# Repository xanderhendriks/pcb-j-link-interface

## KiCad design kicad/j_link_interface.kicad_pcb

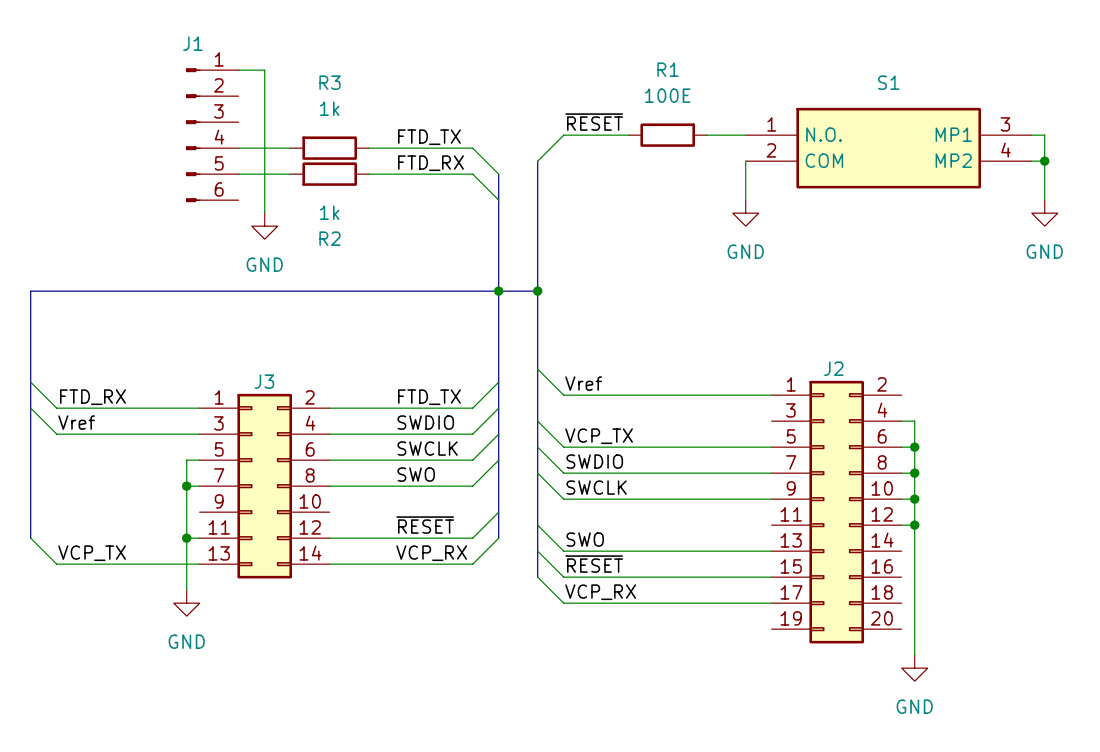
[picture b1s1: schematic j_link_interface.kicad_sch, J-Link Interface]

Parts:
J1: Conn_01x05_Pin; PinHeader_1x06_P2.54mm_Vertical; LCSC C3347142
J2: SFH11-PBPC-D10-RA-BK; LCSC C3319874
J3: FTSH-107-01-X-DV-K; SAMTEC_FTSH-107-01-X-DV-K; LCSC C5307809
R1: 100E; R_0603_1608Metric; LCSC C22775
R2, R3: 1k; R_0603_1608Metric; LCSC C21190
S1: EVQP4HB3B; Manufacturer_Part_Number EVQP42B3M; LCSC C485511

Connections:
/FTD_RX: J3.1, R2.1
/FTD_TX: J3.2, R3.1
/SWCLK: J2.9, J3.6
/SWDIO: J2.7, J3.4
/SWO: J2.13, J3.8
/VCP_RX: J2.17, J3.14
/VCP_TX: J2.5, J3.13
/Vref: J2.1, J3.3
/~RESET: J2.15, J3.12, R1.1
GND: J1.1, J2.4, J2.6, J2.8, J2.10, J2.12, J3.5, J3.7, J3.11, S1.2 (COM), S1.3 (MP1), S1.4 (MP2)
unnamed: J1.4, R3.2
unnamed: J1.5, R2.2
unnamed: R1.2, S1.1 (N.O.)

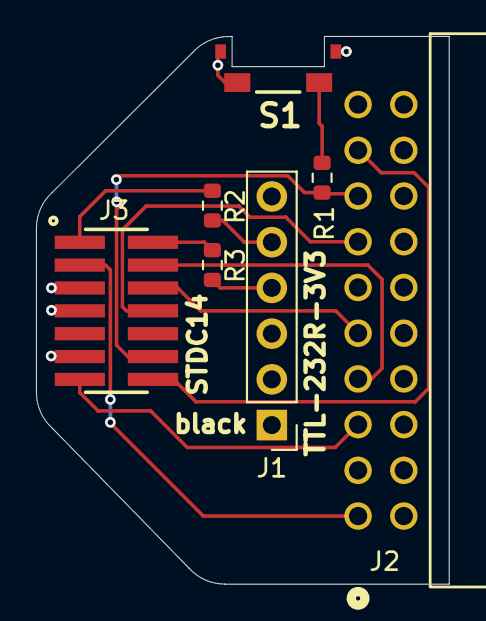
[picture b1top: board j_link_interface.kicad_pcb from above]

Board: 4 copper layers, 22.9 x 30.4 mm, 7 parts (0 on the bottom side), 13 nets.

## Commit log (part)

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2026-03-15 Initial commit. Need to split in J-Trace and J-Link version.
2026-03-16 Updated reset button. Routed all connections.
2026-03-22 Added 2 holes for an enclosure. Moved the reset button.
2026-03-23 Swapped Tx/Rx labels for clarity as they were related to the UARTs on the target board. Some minor updates to traces.
2026-03-31 Added open source hardware logo.
